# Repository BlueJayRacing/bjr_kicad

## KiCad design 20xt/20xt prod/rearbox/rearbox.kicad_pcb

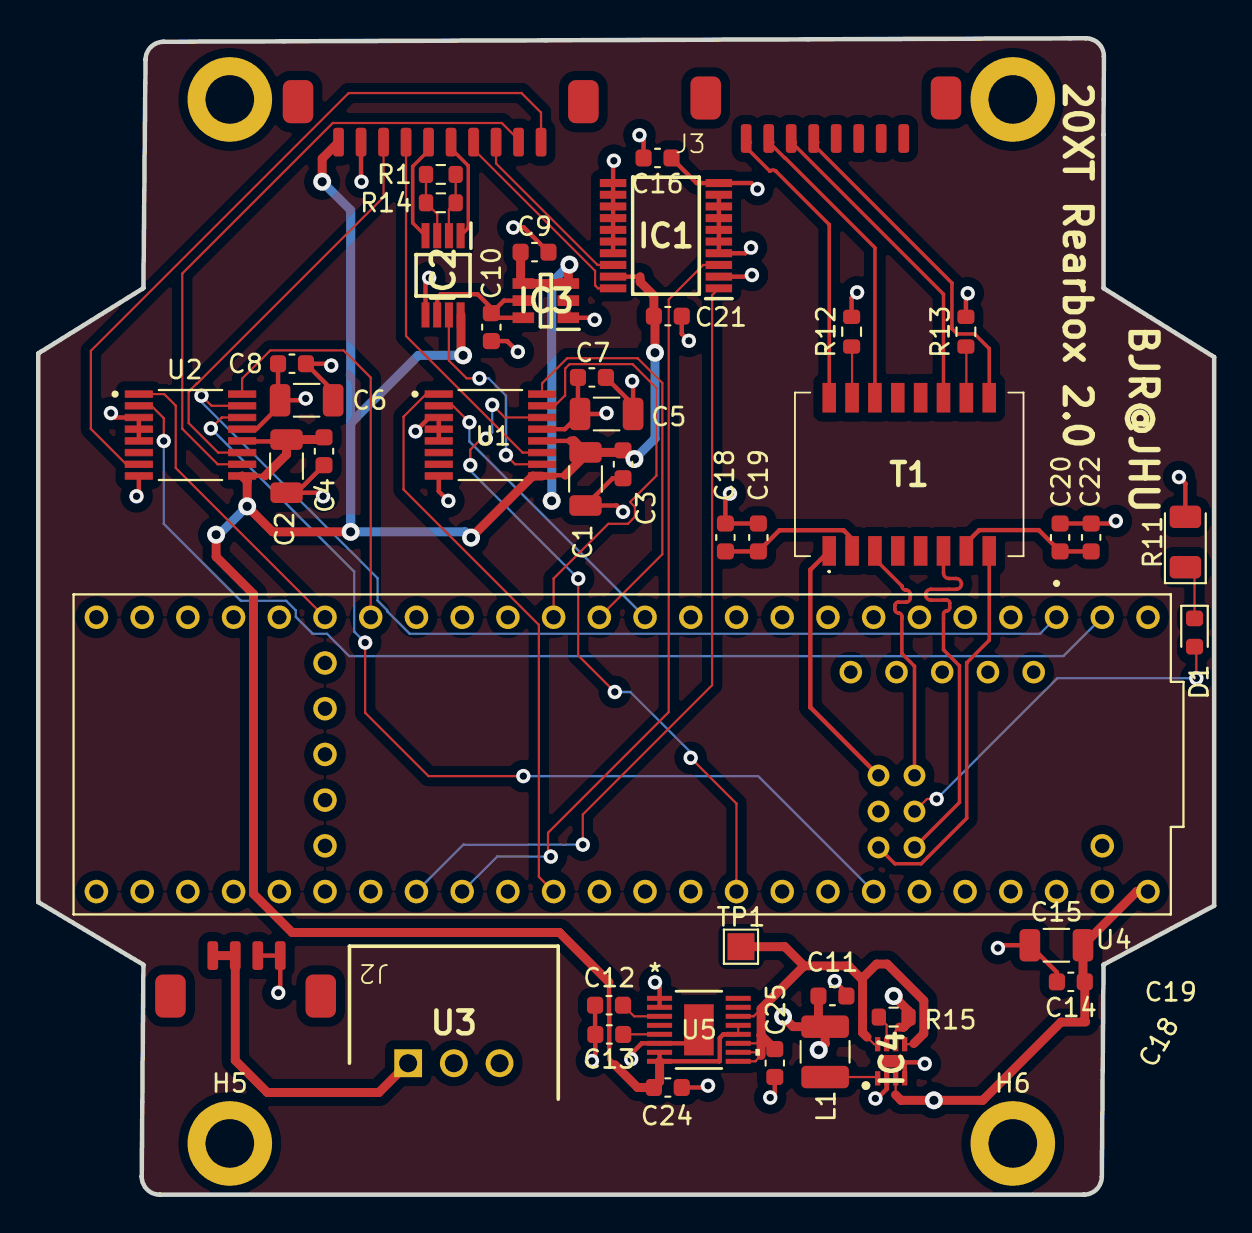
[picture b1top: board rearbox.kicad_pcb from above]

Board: 4 copper layers, 65.3 x 64.2 mm, 49 parts (0 on the bottom side), 48 nets.

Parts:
C1, C2, C5, C6: 100u; C_1206_3216Metric
C3, C4, C7, C8: 0.1u; C_0603_1608Metric
C9, C10, C14, C16, C19, C21, C22: 0.1uF; C_0603_1608Metric
C11: 4.7uF; C_0603_1608Metric
C12, C24: 1 uF; C_0603_1608Metric
C13, C25: 0.1 uF; C_0603_1608Metric
C15: 100uF; C_1206_3216Metric
C18, C20: 1uF; C_0603_1608Metric
D1: LED; LED_0603_1608Metric
H2, H4, H5, H6: MountingHole; MountingHole_2.7mm_M2.5_DIN965_Pad
IC1: TXB0108PWR; SOP65P640X120-20N
IC2: INA821ID; SOP65P490X110-8N
IC3: REF3425QDBVRQ1; SOT95P280X145-6N
IC4: MIC2876-5.5YMT-TR; SON50P200X200X60-9N-D
J1: Conn_01x10; SMD_picoblade_hori_1x10
J2: Conn_01x04; SMD_picoblade_hori_1x04
J3: Conn_01x08; SMD_picoblade_hori_1x08
L1: 1uH; L_1210_3225Metric
R1, R14: 47; R_0603_1608Metric
R11: 330; LED_1206_3216Metric
R12, R13: 75; R_0603_1608Metric
R15: 1M; R_0603_1608Metric
T1: HX1188FNLT
TP1: TestPoint; TestPoint_Pad_1.5x1.5mm
U1, U2: ADS1120IPWR; SOP65P640X120-16N
U3: 173010578
U4: DEV-16771; MODULE_DEV-16771
U5: LT6658AHMSE-5-PBF; MSE_16_ADI

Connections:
2.5v: C10.1, IC2.6 (REF), IC3.5 (OUT_S), IC3.6 (OUT_F)
3v3: C5.1, C6.1, C7.2, C8.2, C16.1, IC1.2 (VCCA), IC1.10 (OE), U1.13 (DVDD), U2.13 (DVDD), U4.3.3V_1 (3.3V)
5.2v: C25.1, IC4.5 (OUTS), IC4.8 (OUT), TP1.1, U5.9 (*OD), U5.10 (VIN2), U5.11 (VIN1), U5.14 (VIN)
5v: C9.1, C11.2, C14.1, C15.2, IC3.3 (EN), IC3.4 (IN), IC4.3 (IN), IC4.6 (EN), L1.2, R15.2, U3.3 (VOUT), U4.VIN
5vref: C1.1, C2.1, C3.2, C4.2, C21.1, C24.1, IC1.19 (VCCB), IC2.8 (+VS), J1.10, U1.9 (REFP0), U1.12 (AVDD), U2.9 (REFP0), U2.12 (AVDD), U5.7 (VOUT2_S), U5.8 (VOUT2_F), U5.12 (VOUT1_F), U5.13 (VOUT1_S)
!CS1: U1.2 (~CS), U4.10 (CS1)
!CS2: U2.2 (~CS), U4.0 (RX1)
/Rx+: J3.6, T1.11 (RX+)
/Rx-: J3.5, T1.9 (RX-)
/Tx+: J3.8, T1.16 (TX+)
/Tx-: J3.7, T1.14 (TX-)
GND: C1.2, C2.2, C3.1, C4.1, C5.2, C6.2, C7.1, C8.1, C9.2, C10.2, C11.1, C12.2, C13.2, C14.2, C15.1, C16.2, C18.1, C19.2, C20.1, C21.2, C22.2, C24.2, C25.2, IC1.4 (A3), IC1.5 (A4), IC1.6 (A5), IC1.7 (A6), IC1.8 (A7), IC1.9 (A8), IC1.11 (GND), IC1.12 (B8), IC1.13 (B7), IC1.14 (B6), IC1.15 (B5), IC1.16 (B4), IC1.17 (B3), IC2.5 (-VS), IC3.1 (GND_F), IC3.2 (GND_S), IC4.2 (PGND), IC4.4 (AGND), IC4.9 (EP), J1.9, J2.3, J2.4, R11.2, R12.2, R13.2, U1.3 (CLK), U1.4 (DGND), U1.5 (AVSS), U1.8 (REFN0), U2.3 (CLK), U2.4 (DGND), U2.5 (AVSS), U2.8 (REFN0), U3.2 (GND), U4.GND1 (GND), U4.GND2 (GND__1), U4.GND3 (GND__2), U4.GND4 (GND__3), U4.GND5 (GND__4), U4.USB_GND1 (USB_GND), U4.USB_GND2 (USB_GND__1), U5.1 (GND), U5.2 (GND), U5.6 (GND), U5.EPAD
unnamed: D1.2 (A), U4.LED
unnamed: D1.1 (K), R11.1
unnamed: IC1.1 (A1), U4.40 (A16)
unnamed: IC1.3 (A2), U4.41 (A17)
unnamed: IC2.2 (RG_1), R1.1, R14.1
unnamed: IC2.3 (RG_2), R1.2, R14.2
unnamed: IC4.1 (SW), L1.1
unnamed: IC4.7 (/PG), R15.1
unnamed: J2.1, J2.2, U3.1 (VIN)
unnamed: R13.1, T1.10 (CMT_1)
unnamed: R12.1, T1.15 (CMT_2)
unnamed: C20.2, C22.1, T1.7 (RCT)
unnamed: C18.2, C19.1, T1.2 (TCT)
unnamed: C12.1, U5.3 (BYPASS)
unnamed: C13.1, U5.5 (NR)
Rd+: T1.6 (RD+), U4.R+
Rd-: T1.8 (RD-), U4.R-
SCLK1: U1.1 (SCLK), U4.13 (SCK)
SCLK2: U2.1 (SCLK), U4.27 (A13)
SDI1: U1.16 (DIN), U4.11 (MOSI)
SDI2: U2.16 (DIN), U4.26 (A12)
SDO1: U1.15 (DOUT/~DRDY), U4.12 (MISO)
SDO2: U2.15 (DOUT/~DRDY), U4.1 (TX1)
Td+: T1.1 (TD+), U4.T+
Td-: T1.3 (TD-), U4.T-
aux1: J1.1, U2.7 (AIN2)
aux2: J1.2, U2.10 (AIN1)
drdy1: U1.14 (~DRDY), U4.17 (A3)
drdy2: U2.14 (~DRDY), U4.20 (A6)
hall1: IC1.18 (B2), J1.3
hall2: IC1.20 (B1), J1.4
linpot1: J1.7, U1.11 (AIN0/REFP1)
linpot2: J1.8, U2.11 (AIN0/REFP1)
sg: IC2.7 (OUT), U1.10 (AIN1)
sg+: IC2.4 (+IN), J1.6
sg-: IC2.1 (-IN), J1.5

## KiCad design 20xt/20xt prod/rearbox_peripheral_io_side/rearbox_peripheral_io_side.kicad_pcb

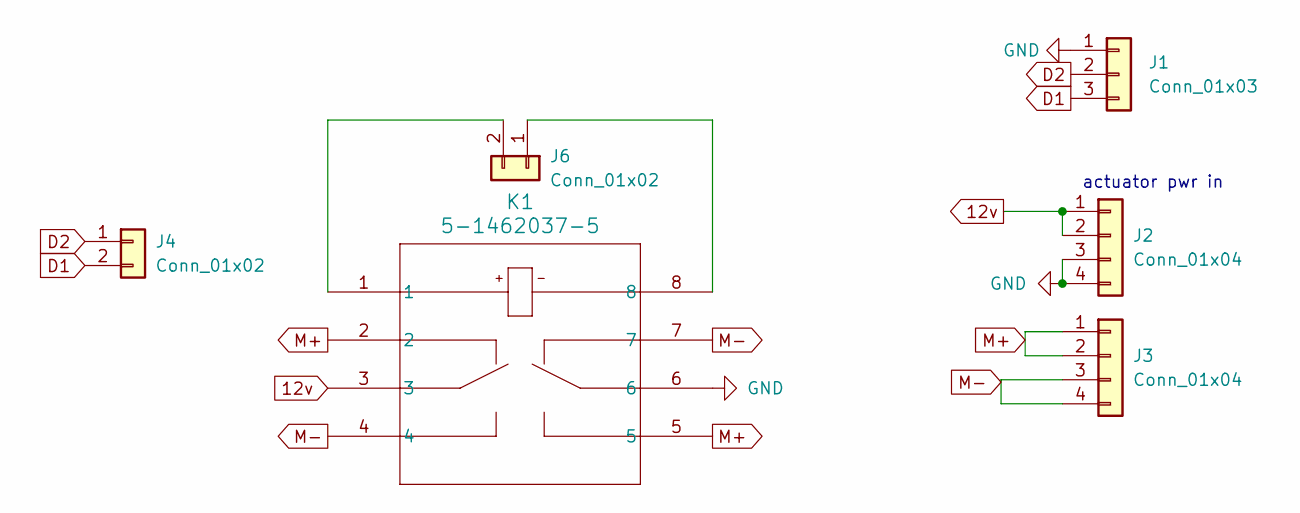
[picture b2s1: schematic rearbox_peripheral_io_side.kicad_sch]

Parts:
J1: Conn_01x03; SMD_picoblade_hori_1x03
J2, J3: Conn_01x04; CONN_T4041017041-000_TEC
J4, J6: Conn_01x02; PinHeader_1x02_P2.54mm_Vertical
K1: 5-1462037-5; RELAY8_SMTJLG_TEC

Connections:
12v: J2.1, J2.2, K1.3
D1: J1.3, J4.2
D2: J1.2, J4.1
GND: J1.1, J2.3, J2.4, K1.6
M+: J3.1, J3.2, K1.2, K1.5
M-: J3.3, J3.4, K1.4, K1.7
unnamed: J6.1, K1.8
unnamed: J6.2, K1.1

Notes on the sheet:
actuator pwr in

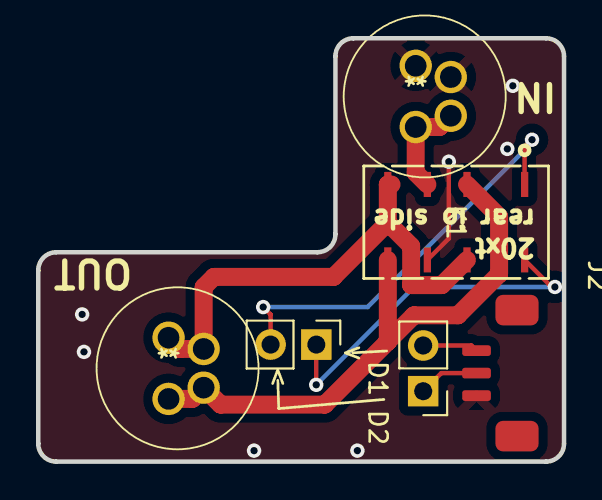
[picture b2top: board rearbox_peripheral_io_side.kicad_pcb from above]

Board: 2 copper layers, 29.2 x 23.5 mm, 6 parts (0 on the bottom side), 8 nets.

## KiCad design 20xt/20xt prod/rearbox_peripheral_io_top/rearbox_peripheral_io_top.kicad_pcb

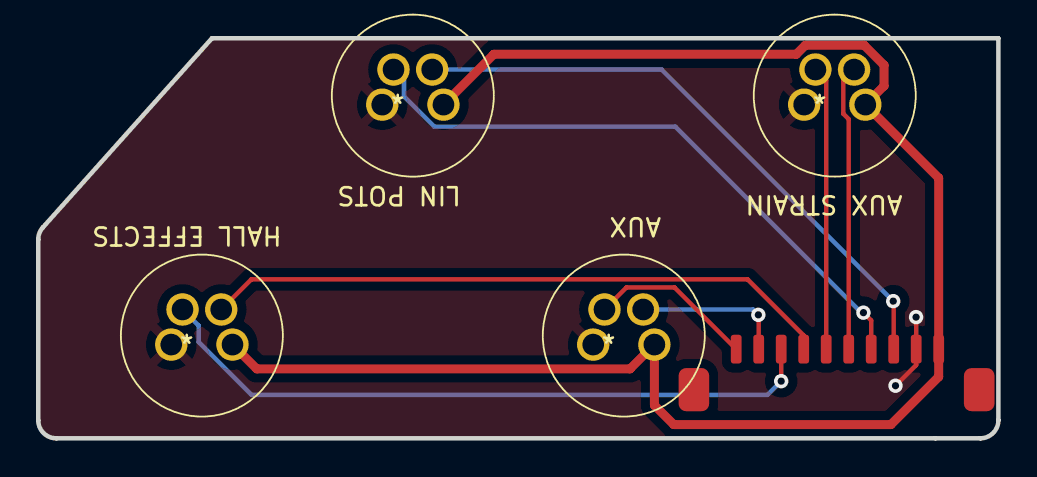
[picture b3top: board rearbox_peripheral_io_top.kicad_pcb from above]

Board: 2 copper layers, 53.3 x 22.2 mm, 5 parts (0 on the bottom side), 10 nets.

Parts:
J2, J3, J4, J5: Conn_01x04; CONN_T4041017041-000_TEC
J6: Conn_01x10; SMD_picoblade_hori_1x10

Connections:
5v: J2.1, J3.1, J4.1, J5.1, J6.10
GND: J2.3, J3.3, J4.3, J5.3, J6.9
unnamed: J2.2, J6.8
unnamed: J2.4, J6.7
unnamed: J3.2, J6.6
unnamed: J3.4, J6.5
unnamed: J4.2, J6.4
unnamed: J4.4, J6.3
unnamed: J5.2, J6.2
unnamed: J5.4, J6.1

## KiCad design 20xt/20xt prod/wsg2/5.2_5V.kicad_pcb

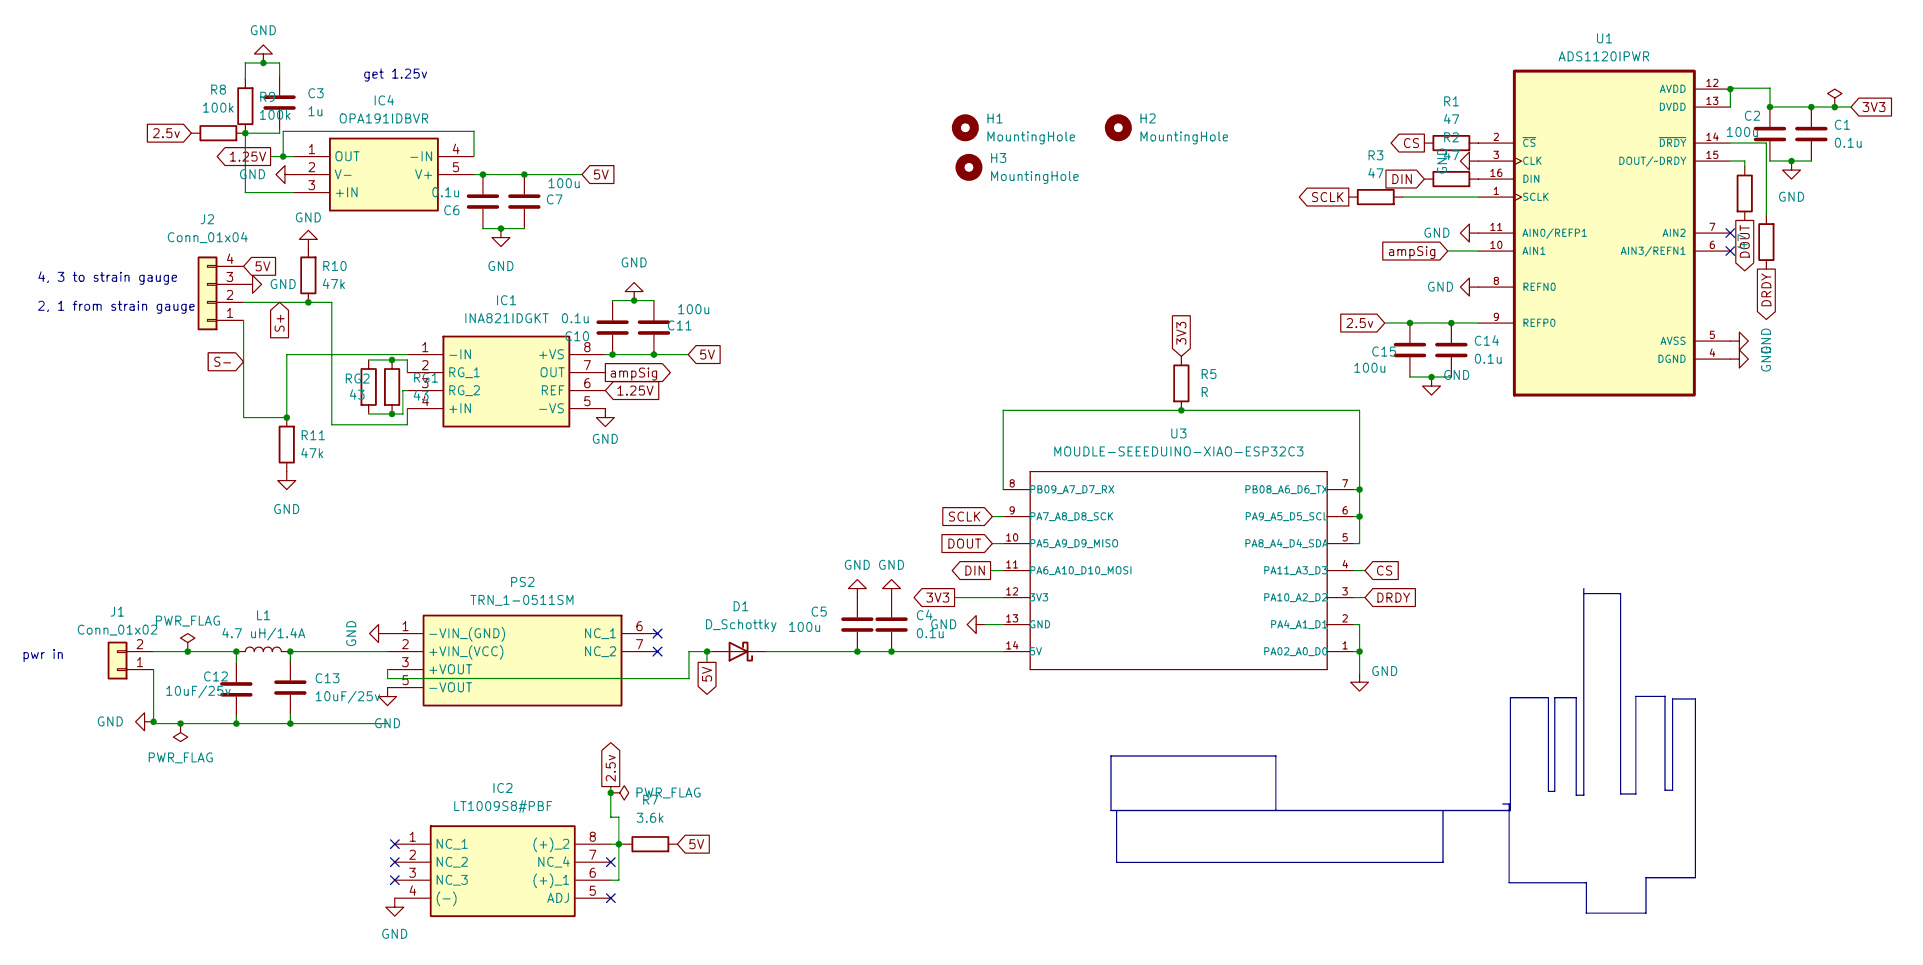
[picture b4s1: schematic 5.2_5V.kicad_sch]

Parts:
C1, C4, C6, C10, C14: 0.1u; C_0603_1608Metric
C2, C5, C7, C11, C15: 100u; C_1206_3216Metric
C3: 1u; C_0603_1608Metric
C12, C13: 10uF/25v; C_1206_3216Metric
D1: D_Schottky; SOT-23-3_1P4X3P040_ONS
H1, H2, H3: MountingHole; MountingHole_2.2mm_M2_Pad
IC1: INA821IDGKT; SOP65P490X110-8N; Mouser Part Number 595-INA821ID
IC2: LT1009S8#PBF; SOIC127P599X175-8N; Mouser Part Number 584-LT1009S8#PBF
IC4: OPA191IDBVR; SOT95P280X145-5N; Mouser Part Number 595-OPA191IDBVR
J1: Conn_01x02; SMD_picoblade_hori_1x02
J2: Conn_01x04; SMD_picoblade_hori_1x04
L1: 4.7 uH/1.4A; L_1008_2520Metric; part number CIGW252010EH4R7MNE
PS2: TRN_1-0511SM; TRN11211SM; Mouser Part Number 495-TRN1-0511SM
R1, R2, R3, R4, R6: 47; R_0603_1608Metric
R5: R; R_0603_1608Metric
R7: 3.6k; R_0805_2012Metric
R8, R9: 100k; R_0603_1608Metric
R10, R11: 47k; R_0603_1608Metric
RG1, RG2: 43; R_0603_1608Metric
U1: ADS1120IPWR; SOP65P640X120-16N
U3: MOUDLE-SEEEDUINO-XIAO-ESP32C3; MODULE_102010388

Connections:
1.25V: IC1.6 (REF), IC4.1 (OUT), IC4.4 (-IN)
2.5v: C14.2, C15.1, IC2.6 ((+)_1), IC2.8 ((+)_2), R7.1, R8.1, U1.9 (REFP0)
3V3: C1.2, C2.1, R5.1, U1.12 (AVDD), U1.13 (DVDD), U3.12 (3V3)
5V: C6.1, C7.2, C10.2, C11.1, D1.2 (A), IC1.8 (+VS), IC4.5 (V+), J2.4, PS2.3 (+VOUT), R7.2
CS: R1.1, U3.4 (PA11_A3_D3)
DIN: R2.1, U3.11 (PA6_A10_D10_MOSI)
DOUT: R4.2, U3.10 (PA5_A9_D9_MISO)
DRDY: R6.1, U3.3 (PA10_A2_D2)
GND: C1.1, C2.2, C3.1, C4.2, C5.1, C6.2, C7.1, C10.1, C11.2, C12.2, C13.1, C14.1, C15.2, IC1.5 (-VS), IC2.4 ((-)), IC4.2 (V-), J1.1, J2.3, PS2.1 (-VIN_(GND)), PS2.5 (-VOUT), R9.2, R10.2, R11.1, U1.3 (CLK), U1.4 (DGND), U1.5 (AVSS), U1.8 (REFN0), U1.11 (AIN0/REFP1), U3.1 (PA02_A0_D0), U3.2 (PA4_A1_D1), U3.13 (GND)
unnamed: C4.1, C5.2, D1.1 (K), U3.14 (5V)
unnamed: IC1.2 (RG_1), RG1.1, RG2.1
unnamed: IC1.3 (RG_2), RG1.2, RG2.2
unnamed: C3.2, IC4.3 (+IN), R8.2, R9.1
unnamed: C12.1, J1.2, L1.1
unnamed: C13.2, L1.2, PS2.2 (+VIN_(VCC))
unnamed: R2.2, U1.16 (DIN)
unnamed: R4.1, U1.15 (DOUT/~DRDY)
unnamed: R3.2, U1.1 (SCLK)
unnamed: R1.2, U1.2 (~CS)
unnamed: R6.2, U1.14 (~DRDY)
unnamed: R5.2, U3.5 (PA8_A4_D4_SDA), U3.6 (PA9_A5_D5_SCL), U3.7 (PB08_A6_D6_TX), U3.8 (PB09_A7_D7_RX)
S+: IC1.4 (+IN), J2.2, R10.1
S-: IC1.1 (-IN), J2.1, R11.2
SCLK: R3.1, U3.9 (PA7_A8_D8_SCK)
ampSig: IC1.7 (OUT), U1.10 (AIN1)

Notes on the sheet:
get 1.25v
pwr in
4, 3 to strain gauge 2, 1 from strain gauge

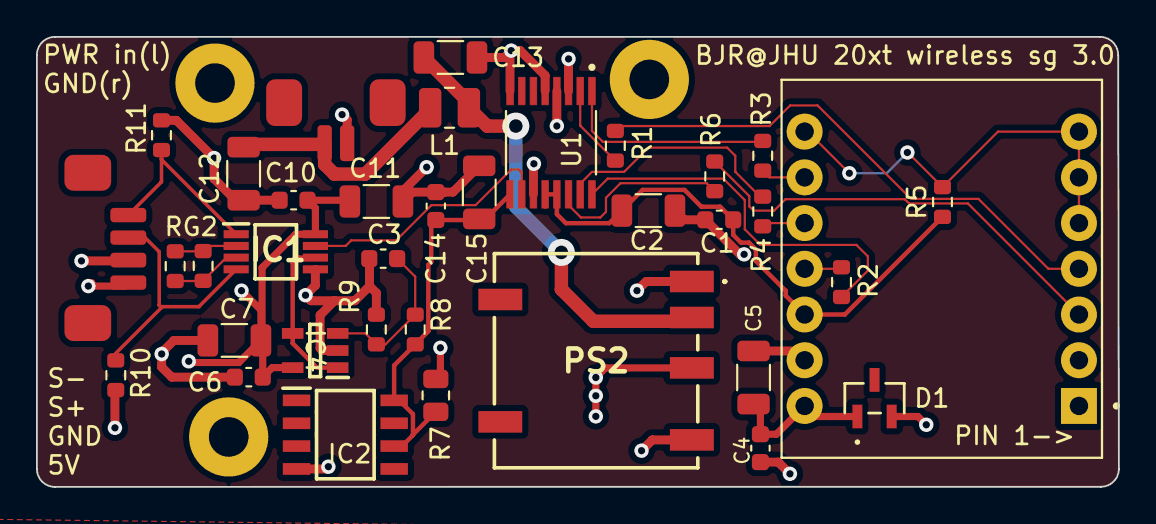
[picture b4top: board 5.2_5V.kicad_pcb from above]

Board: 4 copper layers, 60.1 x 25.0 mm, 39 parts (0 on the bottom side), 25 nets.

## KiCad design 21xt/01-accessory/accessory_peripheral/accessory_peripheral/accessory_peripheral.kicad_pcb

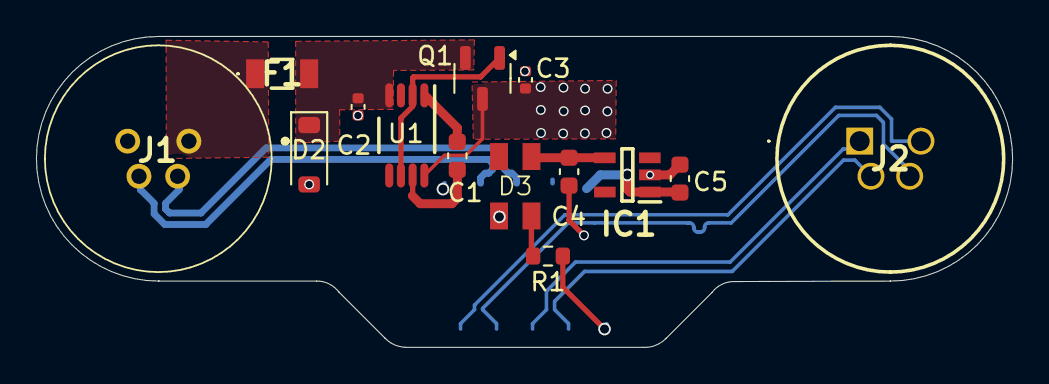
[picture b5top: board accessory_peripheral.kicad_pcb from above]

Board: 4 copper layers, 54.2 x 17.3 mm, 15 parts (1 on the bottom side), 17 nets.

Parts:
C1: 2.2u; C_0603_1608Metric
C2, C3: 100p; C_0402_1005Metric
C4, C5: 10uF; C_0603_1608Metric
D2: DDZ9691-7; D_SOD-123
D3: Adafruit 2659 Neopixel
F1: MF-NSMF050_16X-2; MFNSMF05016X2
IC1: TPS613222ADBVR
J1: T4040014041-000; T4040014041000
J2: T4041017041-000; T4041017041000
J3: 009159010651906; Double Sided Mezzanine Card Edge_Connector Side
Q1: T2N7002BK,LM; SOT-23-3
R1: 300; R_0603_1608Metric
U1: LM74610QDGKRQ1; DGK0008A_N

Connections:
5v cp: C4.1, D3.3 (VDD), IC1.4 (VOUT)
/3V3: C5.2, IC1.1 (SW), J3.5
/5V_USB: C3.1, J3.4, Q1.3 (D), U1.8 (CATHODE)
/LED_control: J3.10, R1.1
/RX_N: J2.2, J3.9
/RX_P: J2.1, J3.8
/TX_N: J2.4, J3.7
/TX_P: J2.3, J3.6
/USB_D_N: J1.2, J3.3
/USB_D_P: J1.4, J3.2
GND: C2.2, C3.2, C4.2, C5.1, D2.2 (A), D3.1 (GND), IC1.2 (GND), J1.3, J3.1
unnamed: C2.1, D2.1 (K), F1.2, Q1.2 (S), U1.4 (ANODE)
unnamed: D3.2 (DIN), R1.2
unnamed: F1.1, J1.1
unnamed: C1.1, U1.7 (VCAPH)
unnamed: C1.2, U1.1 (VCAPL)
gate: Q1.1 (G), U1.2 (GATE_PULL_DOWN), U1.6 (GATE_DRIVE)

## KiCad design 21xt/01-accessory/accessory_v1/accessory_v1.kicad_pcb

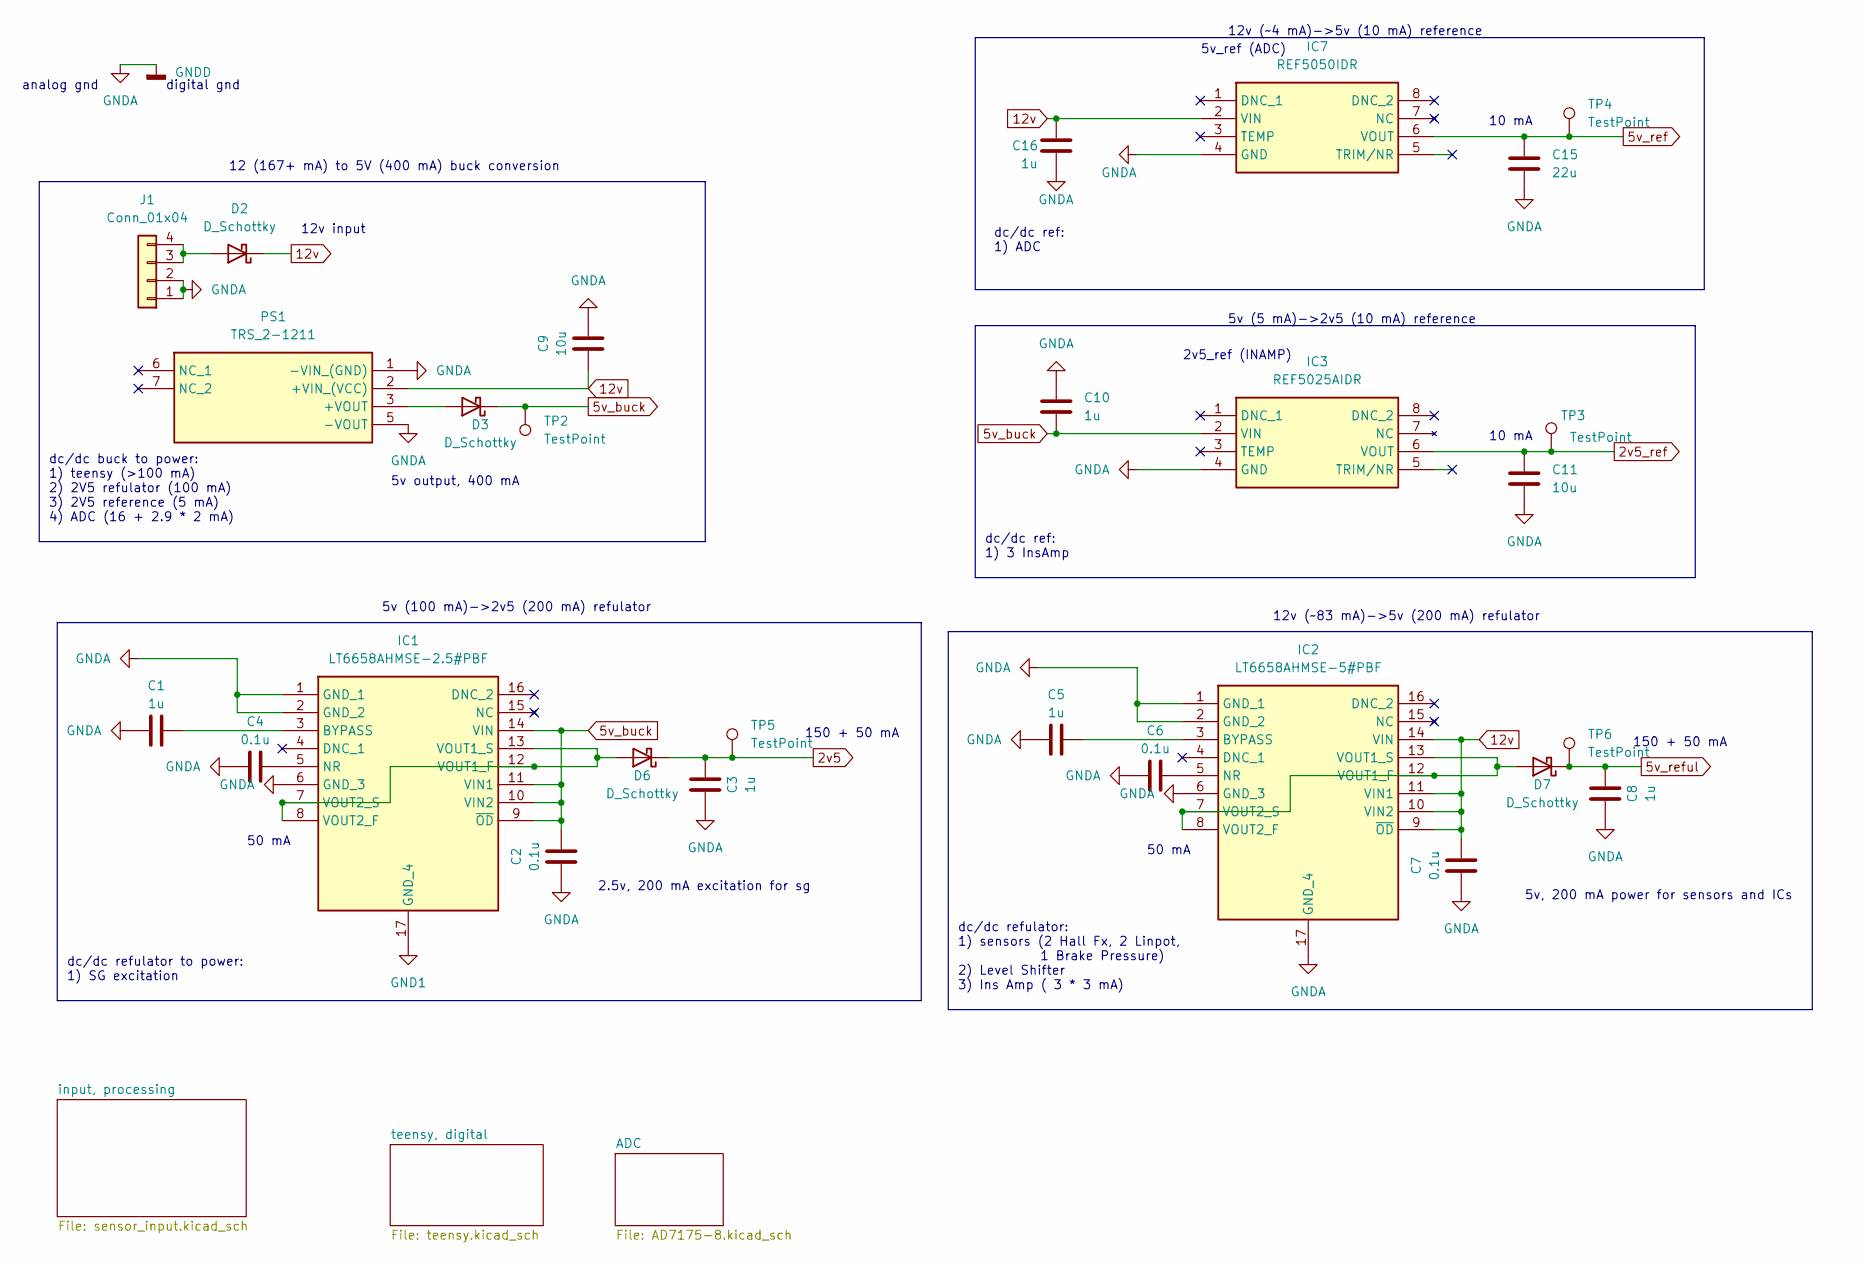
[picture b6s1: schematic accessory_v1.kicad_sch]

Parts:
C1, C3, C5, C8, C10, C16: 1u; C_0603_1608Metric
C2, C4, C6, C7: 0.1u; C_0603_1608Metric
C9: 10u; C_1206_3216Metric
C11: 10u; C_0603_1608Metric
C15: 22u; C_0603_1608Metric
D2: D_Schottky; D_1206_3216Metric
D3, D6, D7: D_Schottky; D_0603_1608Metric
IC1: LT6658AHMSE-2.5#PBF; SOP50P490X110-17N; Mouser Part Number 584-LT6658AHMSE5PBF
IC2: LT6658AHMSE-5#PBF; SOP50P490X110-17N; Mouser Part Number 584-LT6658AHMSE5PBF
IC3: REF5025AIDR; SOIC127P599X175-8N; Mouser Part Number 595-REF5050IDR
IC7: REF5050IDR; SOIC127P599X175-8N; Mouser Part Number 595-REF5050IDR
J1: Conn_01x04; JST_EH_B4B-EH-A_1x04_P2.50mm_Vertical
PS1: TRS_2-1211; CONV_TRS_2-2419; Mouser Part Number 495-TRS2-1211
TP2, TP3, TP4, TP5, TP6: TestPoint; TestPoint_Pad_2.0x2.0mm

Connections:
2v5: C3.2, D6.1 (K), TP5.1; also elsewhere on the board
2v5_ref: C11.1, IC3.6 (VOUT), TP3.1; also elsewhere on the board
5v_buck: C2.2, C10.1, D3.1 (K), IC1.9 (~OD), IC1.10 (VIN2), IC1.11 (VIN1), IC1.14 (VIN), IC3.2 (VIN), TP2.1; also elsewhere on the board
5v_ref: C15.1, IC7.6 (VOUT), TP4.1; also elsewhere on the board
5v_reful: C8.2, D7.1 (K), TP6.1; also elsewhere on the board
12v: C7.2, C9.1, C16.1, D2.1 (K), IC2.9 (~OD), IC2.10 (VIN2), IC2.11 (VIN1), IC2.14 (VIN), IC7.2 (VIN), PS1.2 (+VIN_(VCC)); also elsewhere on the board
GND1: IC1.17 (GND_4)
GNDA: C1.1, C2.1, C3.1, C4.1, C5.1, C6.1, C7.1, C8.1, C9.2, C10.2, C11.2, C15.2, C16.2, IC1.1 (GND_1), IC1.2 (GND_2), IC1.6 (GND_3), IC2.1 (GND_1), IC2.2 (GND_2), IC2.6 (GND_3), IC2.17 (GND_4), IC3.4 (GND), IC7.4 (GND), J1.1, J1.2, PS1.1 (-VIN_(GND)), PS1.5 (-VOUT); also elsewhere on the board
unnamed: D2.2 (A), J1.3, J1.4
unnamed: D3.2 (A), PS1.3 (+VOUT)
unnamed: D6.2 (A), IC1.7 (VOUT2_S), IC1.8 (VOUT2_F), IC1.12 (VOUT1_F), IC1.13 (VOUT1_S)
unnamed: D7.2 (A), IC2.7 (VOUT2_S), IC2.8 (VOUT2_F), IC2.12 (VOUT1_F), IC2.13 (VOUT1_S)
unnamed: C1.2, IC1.3 (BYPASS)
unnamed: C4.2, IC1.5 (NR)
unnamed: C5.2, IC2.3 (BYPASS)
unnamed: C6.2, IC2.5 (NR)

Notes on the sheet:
2.5v, 200 mA excitation for sg
150 + 50 mA
50 mA
dc/dc ref: 1) 3 InsAmp
5v (5 mA)->2v5 (10 mA) reference
10 mA
analog gnd
12 (167+ mA) to 5V (400 mA) buck conversion
5v_ref (ADC)
12v input
5v, 200 mA power for sensors and ICs
5v (100 mA)->2v5 (200 mA) refulator
dc/dc refulator: 1) sensors (2 Hall Fx, 2 Linpot, 1 Brake Pressure) 2) Level Shifter 3) Ins Amp ( 3 * 3 mA)
2v5_ref (INAMP)
12v (~83 mA)->5v (200 mA) refulator
digital gnd
dc/dc ref: 1) ADC
dc/dc buck to power: 1) teensy (>100 mA) 2) 2V5 refulator (100 mA) 3) 2V5 reference (5 mA) 4) ADC (16 + 2.9 * 2 mA)
5v output, 400 mA
12v (~4 mA)->5v (10 mA) reference
dc/dc refulator to power: 1) SG excitation

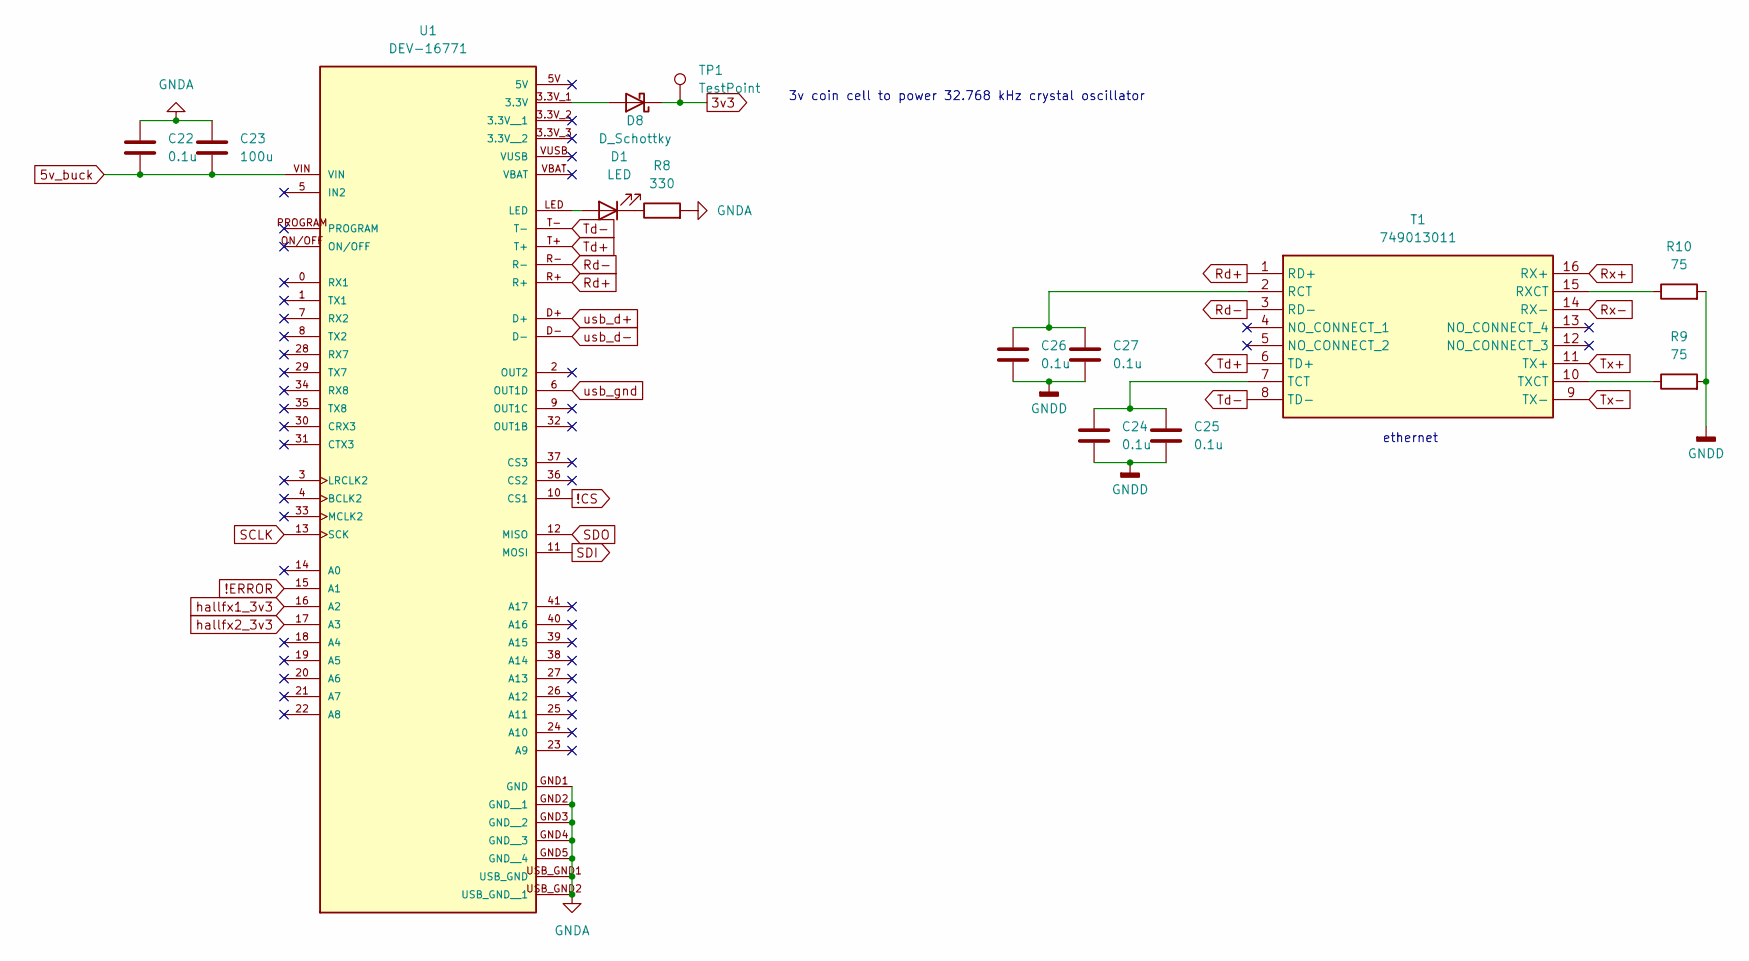
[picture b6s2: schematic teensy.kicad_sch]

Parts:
C22, C24, C25, C26, C27: 0.1u; C_0603_1608Metric
C23: 100u; C_1206_3216Metric
D1: LED; D_0603_1608Metric
D8: D_Schottky; D_0603_1608Metric
R8: 330; R_0603_1608Metric
R9, R10: 75; R_0603_1608Metric
T1: 749013011; Mouser Part Number 710-749013011
TP1: TestPoint; TestPoint_Pad_2.0x2.0mm
U1: DEV-16771; MODULE_DEV-16771; PARTREV 4.1

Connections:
3v3: D8.1 (K), TP1.1; also elsewhere on the board
5v_buck: C22.2, C23.2, U1.VIN; also elsewhere on the board
!CS: U1.10 (CS1); also elsewhere on the board
!ERROR: U1.15 (A1); also elsewhere on the board
GNDA: C22.1, C23.1, C24.2, C25.2, C26.2, C27.2, R8.2, R9.2, R10.2, U1.GND1 (GND), U1.GND2 (GND__1), U1.GND3 (GND__2), U1.GND4 (GND__3), U1.GND5 (GND__4), U1.USB_GND1 (USB_GND), U1.USB_GND2 (USB_GND__1); also elsewhere on the board
unnamed: D1.2 (A), U1.LED
unnamed: D1.1 (K), R8.1
unnamed: D8.2 (A), U1.3.3V_1 (3.3V)
unnamed: C26.1, C27.1, T1.2 (RCT)
unnamed: R10.1, T1.15 (RXCT)
unnamed: C24.1, C25.1, T1.7 (TCT)
unnamed: R9.1, T1.10 (TXCT)
Rd+: T1.1 (RD+), U1.R+
Rd-: T1.3 (RD-), U1.R-
Rx+: T1.16 (RX+); also elsewhere on the board
Rx-: T1.14 (RX-); also elsewhere on the board
SCLK: U1.13 (SCK); also elsewhere on the board
SDI: U1.11 (MOSI); also elsewhere on the board
SDO: U1.12 (MISO); also elsewhere on the board
Td+: T1.6 (TD+), U1.T+
Td-: T1.8 (TD-), U1.T-
Tx+: T1.11 (TX+); also elsewhere on the board
Tx-: T1.9 (TX-); also elsewhere on the board
hallfx1_3v3: U1.16 (A2); also elsewhere on the board
hallfx2_3v3: U1.17 (A3); also elsewhere on the board
usb_d+: U1.D+; also elsewhere on the board
usb_d-: U1.D-; also elsewhere on the board
usb_gnd: U1.6 (OUT1D); also elsewhere on the board

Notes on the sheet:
3v coin cell to power 32.768 kHz crystal oscillator
ethernet

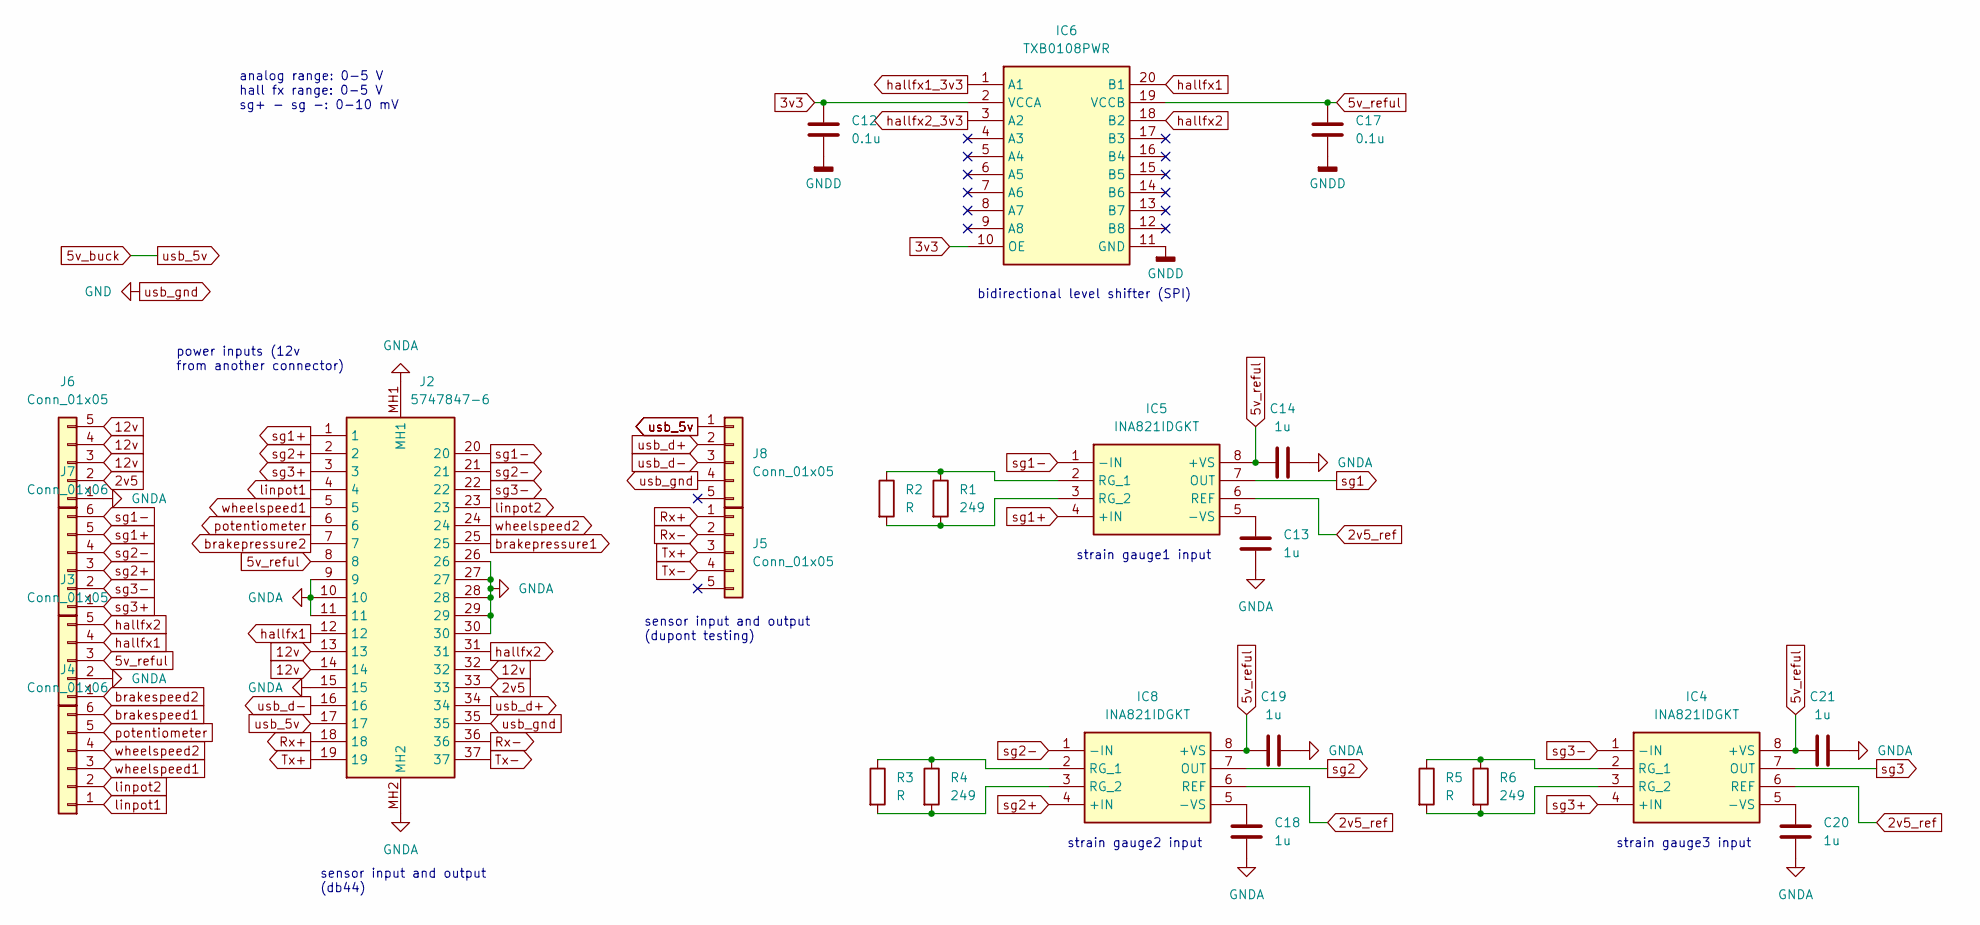
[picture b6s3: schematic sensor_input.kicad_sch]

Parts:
C12, C17: 0.1u; C_0603_1608Metric
C13, C14, C18, C19, C20, C21: 1u; C_0603_1608Metric
IC4, IC5, IC8: INA821IDGKT; SOP65P490X110-8N; Mouser Part Number 595-INA821IDGKT
IC6: TXB0108PWR; SOP65P640X120-20N; Mouser Part Number 595-TXB0108PWR
J2: 5747847-6; 57478476; Manufacturer_Part_Number 5747847-6; Mouser Part Number 571-5747847-6
J3, J5, J6, J8: Conn_01x05; JST_EH_B5B-EH-A_1x05_P2.50mm_Vertical
J4, J7: Conn_01x06; JST_EH_B6B-EH-A_1x06_P2.50mm_Vertical
R1, R4, R6: 249; R_0603_1608Metric
R2, R3, R5: R; R_0603_1608Metric

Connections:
2v5: J2.33, J6.2; also elsewhere on the board
2v5_ref: IC4.6 (REF), IC5.6 (REF), IC8.6 (REF); also elsewhere on the board
3v3: C12.1, IC6.2 (VCCA), IC6.10 (OE); also elsewhere on the board
5v_buck: J2.17, J8.1; also elsewhere on the board
5v_reful: C14.1, C17.1, C19.1, C21.1, IC4.8 (+VS), IC5.8 (+VS), IC6.19 (VCCB), IC8.8 (+VS), J2.8, J3.3; also elsewhere on the board
12v: J2.13, J2.14, J2.32, J6.3, J6.4, J6.5; also elsewhere on the board
GNDA: C12.2, C13.2, C14.2, C17.2, C18.2, C19.2, C20.2, C21.2, IC6.11 (GND), J2.9, J2.10, J2.11, J2.15, J2.26, J2.27, J2.28, J2.29, J2.30, J2.MH1, J2.MH2, J3.2, J6.1; also elsewhere on the board
unnamed: C20.1, IC4.5 (-VS)
unnamed: IC4.2 (RG_1), R5.1, R6.1
unnamed: IC4.3 (RG_2), R5.2, R6.2
unnamed: C13.1, IC5.5 (-VS)
unnamed: IC5.2 (RG_1), R1.1, R2.1
unnamed: IC5.3 (RG_2), R1.2, R2.2
unnamed: C18.1, IC8.5 (-VS)
unnamed: IC8.2 (RG_1), R3.1, R4.1
unnamed: IC8.3 (RG_2), R3.2, R4.2
Rx+: J2.18, J5.1; also elsewhere on the board
Rx-: J2.36, J5.2; also elsewhere on the board
Tx+: J2.19, J5.3; also elsewhere on the board
Tx-: J2.37, J5.4; also elsewhere on the board
brakepressure1: J2.25; also elsewhere on the board
brakepressure2: J2.7; also elsewhere on the board
brakespeed1: J4.6
brakespeed2: J3.1
hallfx1: IC6.20 (B1), J2.12, J3.4
hallfx1_3v3: IC6.1 (A1); also elsewhere on the board
hallfx2: IC6.18 (B2), J2.31, J3.5
hallfx2_3v3: IC6.3 (A2); also elsewhere on the board
linpot1: J2.4, J4.1; also elsewhere on the board
linpot2: J2.23, J4.2; also elsewhere on the board
potentiometer: J2.6, J4.5; also elsewhere on the board
sg1: IC5.7 (OUT); also elsewhere on the board
sg1+: IC5.4 (+IN), J2.1, J7.5
sg1-: IC5.1 (-IN), J2.20, J7.6
sg2: IC8.7 (OUT); also elsewhere on the board
sg2+: IC8.4 (+IN), J2.2, J7.3
sg2-: IC8.1 (-IN), J2.21, J7.4
sg3: IC4.7 (OUT); also elsewhere on the board
sg3+: IC4.4 (+IN), J2.3, J7.1
sg3-: IC4.1 (-IN), J2.22, J7.2
usb_d+: J2.34, J8.2; also elsewhere on the board
usb_d-: J2.16, J8.3; also elsewhere on the board
usb_gnd: J2.35, J8.4; also elsewhere on the board
wheelspeed1: J2.5, J4.3; also elsewhere on the board
wheelspeed2: J2.24, J4.4; also elsewhere on the board

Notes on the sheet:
bidirectional level shifter (SPI)
power inputs (12v from another connector)
strain gauge3 input
strain gauge1 input
sensor input and output (db44)
strain gauge2 input
analog range: 0-5 V hall fx range: 0-5 V sg+ - sg -: 0-10 mV
sensor input and output (dupont testing)
